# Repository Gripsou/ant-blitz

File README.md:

# ant-blitz
UV meter based on STM32

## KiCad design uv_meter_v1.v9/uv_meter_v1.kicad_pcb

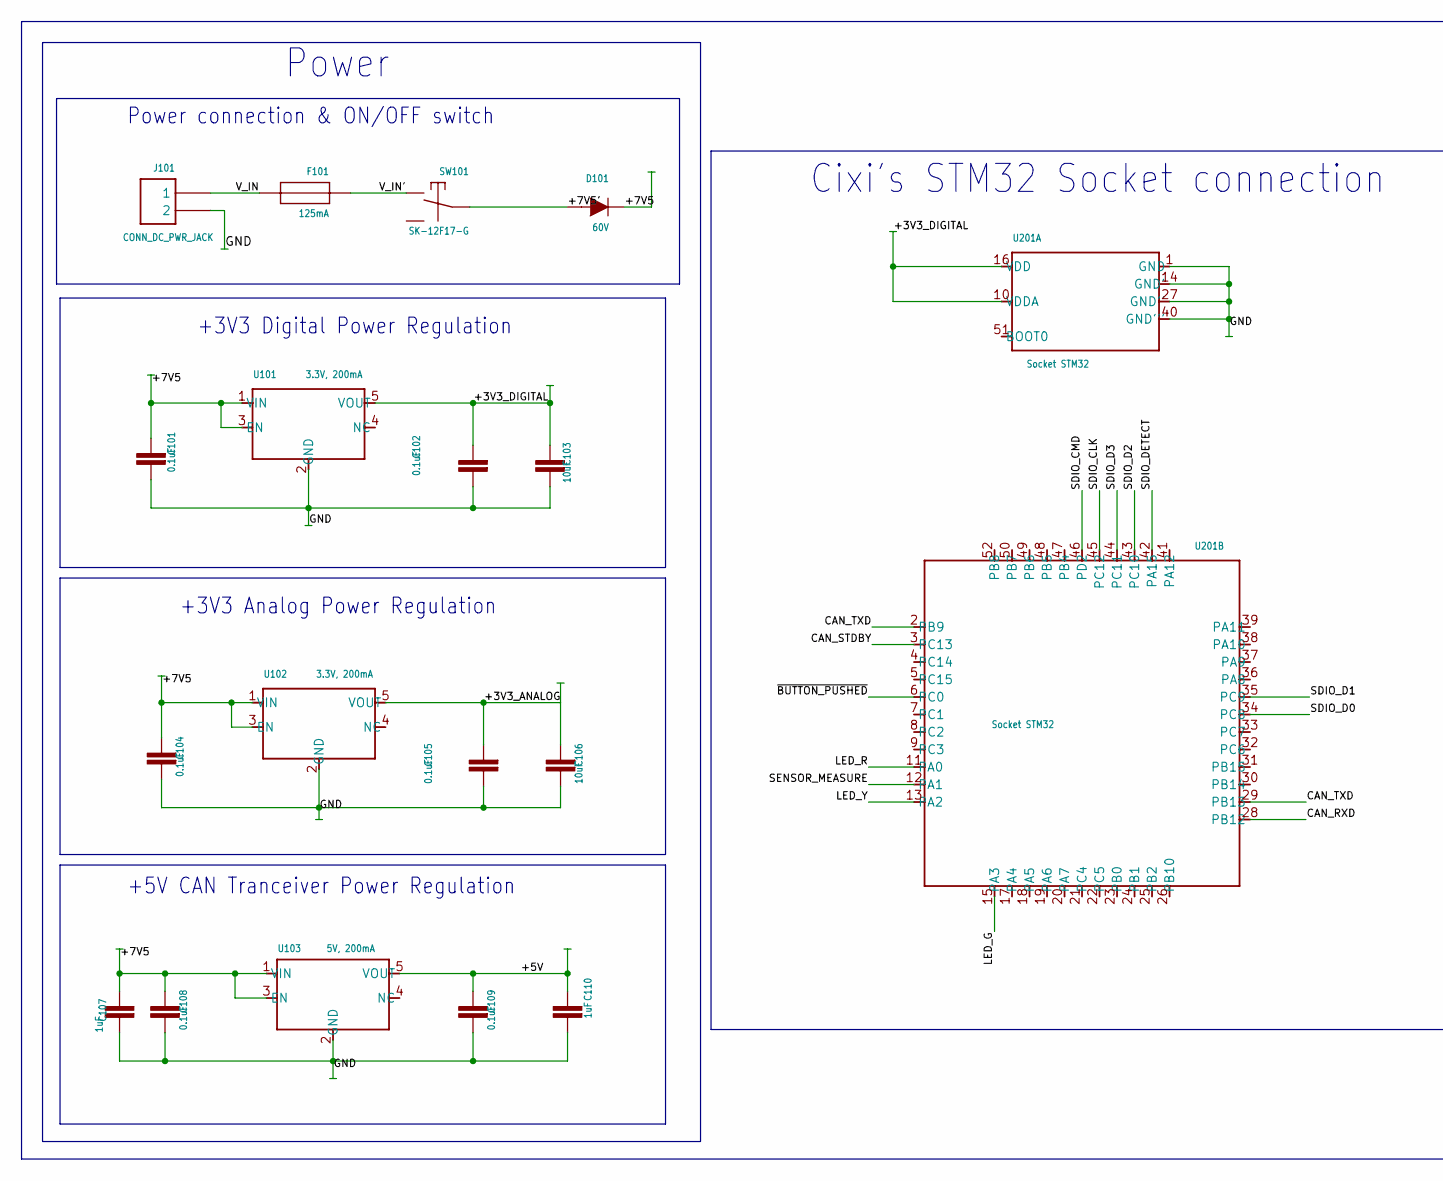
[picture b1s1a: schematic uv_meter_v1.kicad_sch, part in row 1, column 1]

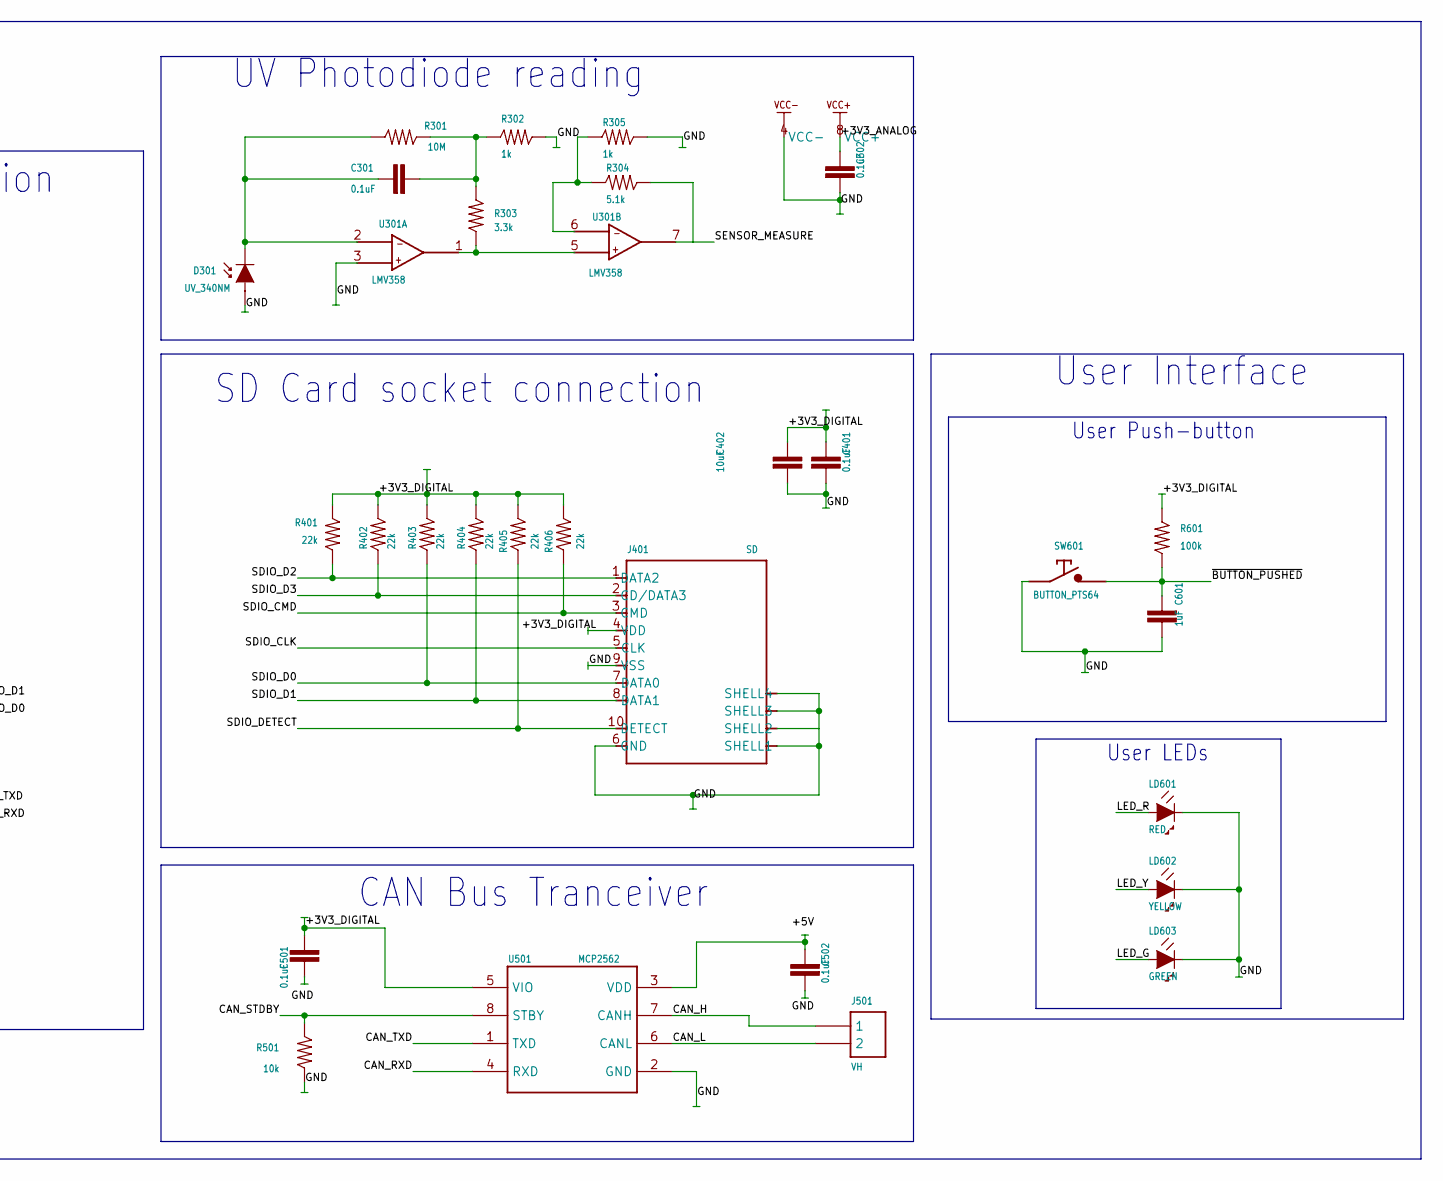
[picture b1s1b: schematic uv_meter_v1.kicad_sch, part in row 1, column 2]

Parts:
C101, C102, C104, C105, C108, C109, C301, C302, C401, C501, C502: 0.1uF; 0805_GRM
C103, C106, C402: 10uF; 0805_GRM
C107, C110, C601: 1uF; 0805_GRM
D101: 60V; SOD123_ST
D301: UV_340NM; PHOTODIODE_MOLDED
F101: 125mA; FUSE_1206
J101: CONN_DC_PWR_JACK
J401: SD; CONN_SD_5033981892
J501: VH; JST_VH_2F_SIDE
LD601: RED; LED_0805
LD602: YELLOW; LED_0805
LD603: GREEN; LED_0805
R301: 10M; RES_0805_ERJ
R302, R305: 1k; RES_0805_ERJ
R303: 3.3k; RES_0805_ERJ
R304: 5.1k; RES_0805_VISHAY
R401, R402, R403, R404, R405, R406: 22k; RES_0805_ERJ
R501: 10k; RES_0805_ERJ
R601: 100k; RES_0805_ERJ
SW101: SK-12F17-G; COMMUTATOR_SK-12F17-G
SW601: BUTTON_PTS64; BUTTON_PUSH_CK
U101, U102: 3.3V, 200mA; SOT23-5
U103: 5V, 200mA; SOT23-5
U201: Socket STM32; SOCKET_STM32
U301: LMV358; SOIC8
U501: MCP2562; SO_8

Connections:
+3V3_ANALOG: C105.1 (2), C106.1 (2), C302.2 (1), U102.5 (VOUT), U301.8 (VCC+)
+3V3_DIGITAL: C102.1 (2), C103.1 (2), C401.2 (1), C402.2 (1), C501.1 (2), J401.4 (VDD), R401.2, R402.2, R403.2, R404.2, R405.2, R406.2, R601.2, U101.5 (VOUT), U201.10 (VDDA), U201.16 (VDD), U501.5 (VIO)
+7V5: C101.1 (2), C104.1 (2), C107.1 (2), C108.1 (2), D101.K, U101.1 (VIN), U101.3 (EN), U102.1 (VIN), U102.3 (EN), U103.1 (VIN), U103.3 (EN)
+7V5': D101.A, SW101.IN
CAN_H: J501.1, U501.7 (CANH)
CAN_L: J501.2, U501.6 (CANL)
CAN_RXD: U201.28 (PB12), U501.4 (RXD)
CAN_STDBY: R501.2, U201.3 (PC13), U501.8 (STBY)
CAN_TXD: U201.2 (PB9), U201.29 (PB13), U501.1 (TXD)
GND: C101.2 (1), C102.2 (1), C103.2 (1), C104.2 (1), C105.2 (1), C106.2 (1), C107.2 (1), C108.2 (1), C109.2 (1), C110.2 (1), C302.1 (2), C401.1 (2), C402.1 (2), C501.2 (1), C502.2 (1), C601.2 (1), D301.2 (A), J101.2, J101.3 (2), J401.6 (GND), J401.9 (VSS), J401.SH1 (SHELL1), J401.SH2 (SHELL2), J401.SH3 (SHELL3), J401.SH4 (SHELL4), LD601.1 (K), LD602.1 (K), LD603.1 (K), R302.2, R305.2, R501.1, SW601.1 (C), SW601.2 (C), U101.2 (GND), U102.2 (GND), U103.2 (GND), U201.1 (GND), U201.14 (GND'), U201.27 (GND''), U201.40 (GND'''), U301.3 (IN+), U301.4 (VCC-), U501.2 (GND)
LED_G: LD603.2 (A), U201.15 (PA3)
LED_R: LD601.2 (A), U201.11 (PA0)
LED_Y: LD602.2 (A), U201.13 (PA2)
unnamed: R303.1, U301.1 (OUT), U301.5 (IN+)
unnamed: C301.1 (2), R301.2, R302.1, R303.2
unnamed: C301.2 (1), D301.1 (K), R301.1, U301.2 (IN-)
unnamed: R304.1, R305.1, U301.6 (IN-)
SDIO_CLK: J401.5 (CLK), U201.45 (PC12)
SDIO_CMD: J401.3 (CMD), R406.1, U201.46 (PD2)
SDIO_D0: J401.7 (DATA0), R403.1, U201.34 (PC8)
SDIO_D1: J401.8 (DATA1), R404.1, U201.35 (PC9)
SDIO_D2: J401.1 (DATA2), R401.1, U201.43 (PC10)
SDIO_D3: J401.2 (CD/DATA3), R402.1, U201.44 (PC11)
SDIO_DETECT: J401.10 (DETECT), R405.1, U201.42 (PA15)
SENSOR_MEASURE: R304.2, U201.12 (PA1), U301.7 (OUT)
V_IN: F101.1, J101.1
V_IN': F101.2, SW101.OUT_L (OUT_1)
~BUTTON_PUSHED: C601.1 (2), R601.1, SW601.3 (T), SW601.4 (T), U201.6 (PC0)

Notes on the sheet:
Cixi's STM32 Socket connection
User Interface
+3V3 Digital Power Regulation
+5V CAN Tranceiver Power Regulation
User Push-button
SD Card socket connection
UV Photodiode reading
CAN Bus Tranceiver
Power connection & ON/OFF switch
Power
User LEDs
+3V3 Analog Power Regulation

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
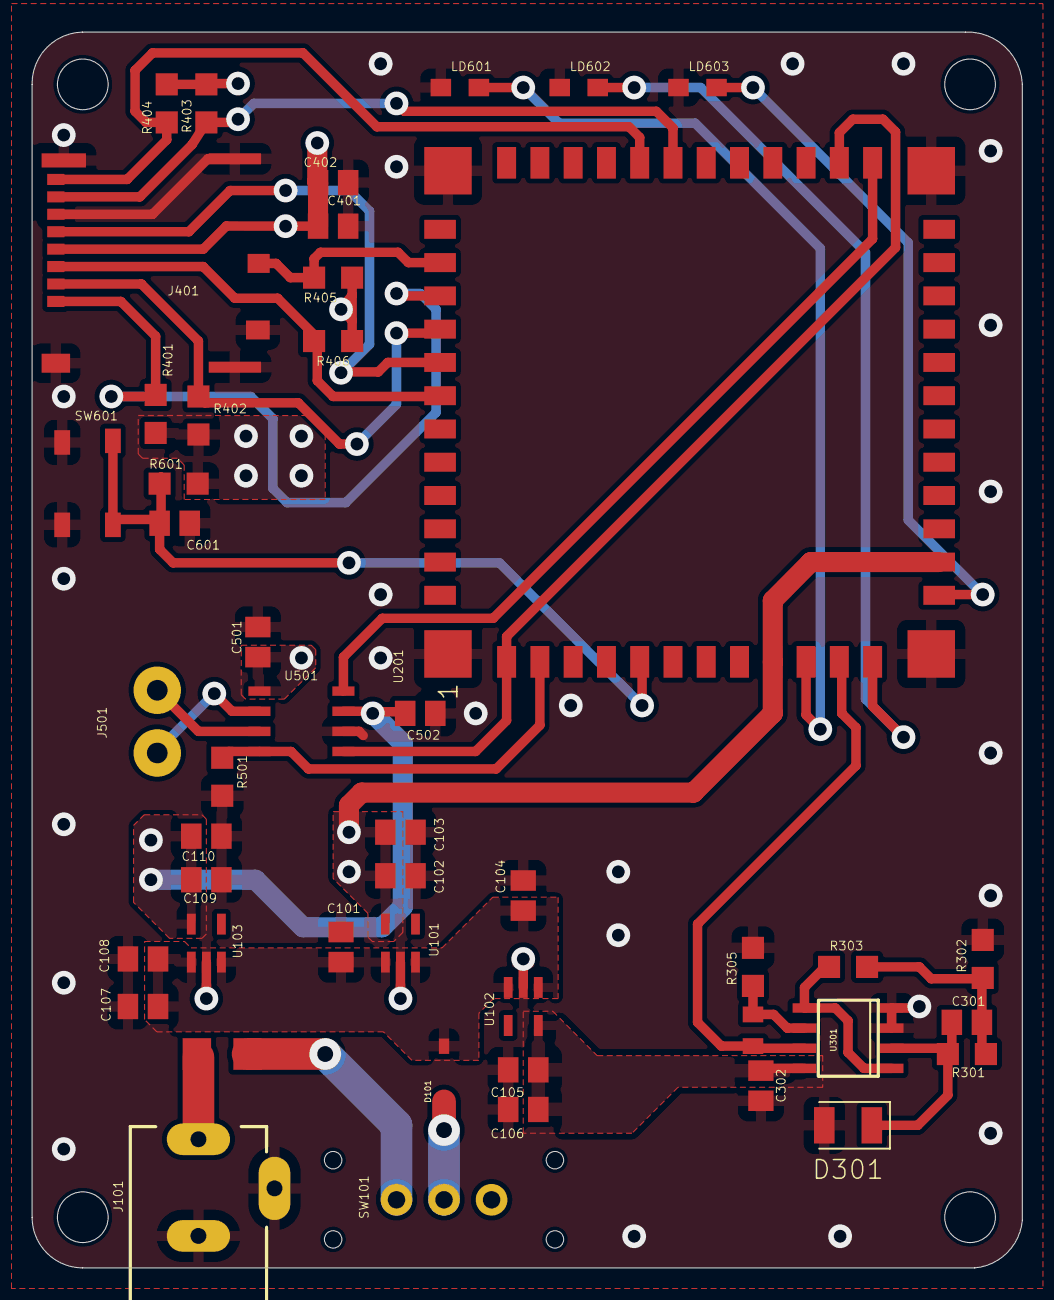
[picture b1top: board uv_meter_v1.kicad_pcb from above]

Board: 2 copper layers, 62.5 x 78.0 mm, 51 parts (0 on the bottom side), 29 nets.

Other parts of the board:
UNK_HOLE_0: dummyfp0
UNK_HOLE_1: dummyfp1
UNK_HOLE_2: dummyfp2
UNK_HOLE_3: dummyfp3

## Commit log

2025-01-14 Initial commit
    * Add "README.md"
    * Add ".gitignore" for KiCad
    * Add LICENSE
2025-01-14 Import project from EAGLE
    Import EAGLE project to KiCad 9.
2025-01-21 Move project created in KiCad 9 rc1 to dedicated forlder
    Since the project seems to have issues, it is better to isolte it in its specific folder and try it again when KiCad v9.0.0 or even v9.0.1 is released.
2025-01-21 Try new project import in KiCad 8
    Use KiCad v8.0.8 to import project and see if it fixes the 3D model issues. If yes, we might just get rid of the previous KiCad v9 rc1 import and update it to v9 once it is released
2025-01-21 Design importation fix
    * Import from Eagle has some inconsistency such as copper exclusion being attributed to "F.Courtyard" instead of "Margin".
    * Add margin where it is supposed to be.
    * Add some 3D models : local footprint library links to KiCad 8 3D models library as much as possible.
2025-01-22 Fix STM32 Socket and LDO symbols
    * Remove all `polyline` elements from symbols when not usefull.
    * Fix pin lenght, texts size and overall positions since they are not on a
    metric grid just like it is supposed to be in this particular case.
    * Add background color so the symbol looks better.
    * LDO +3V3 and +1V8 now derive from the +5V one.
2025-01-22 Update schematic from library
    Since some symbols have been updated to look better and for later and easier
    updates a schematic update from library was required.
    NOTE :
    The current goal is to fix all symbols and schematic but it should look like
    what the original project was. No symbol redesign is to be performed at this
    stage : we will tag this as the V0 since the PCB has been assembled in the
2025-01-22 Update all vias positions
    Import from original project has placed geometric shapes on an imperial grid.
    Therefore, we need to place them back on a metric grid.
    => this has been done for all vias in the current commit.
2025-02-24 Update LMV358 symbol
    * Update LMV358 symbol in local library : use shapes that allow to fill
    symbol and break power supply sub-symbol into 2 different entities
    for ease of use reasons.
    * Update design schematic accordingly.
2025-02-24 Add one picture of actual PCB
    Add a picture of the system as it was assembled. The picture shows the
    photodiode reading SMD assembly.
2025-03-01 Update to KiCad V9.0.0
    Update project files to KiCad V9.0.0. Apparently a few changes were brought to the software and configuration files since the release candidate 1
2025-04-15 Update Power symbols in schematic
    * Remove old power "symbols" created with labels and make use of KiCad's
    power symbols from standard library instead
    * Place unconnected marks where required. This will comply with KiCad's
    standards if any ERC check is performed
2025-04-20 Update MCP2562 symbol
    Update MCP2562 CAN transceiver symbol so it corresponds to my KiCad standards and look better in schematic
2025-05-21 Update Capacitors symbols in library
    * Create generic capacitor symbol out of 100 nF one.
    * Update symbol's graphical elements so they are handled in an easier
    way in KiCad.
    * Make all capcitor values derivatives from the generic "C" symbol
    i.e. 100 nF, 1 µF and 10 µF.
2025-05-21 Update Resistor symbols in library
    * Create generic resistor symbol
    * Update symbol's graphical elements so they are handled in an easier
    way in KiCad.
    * Make all resistor values derivatives from the generic "R" symbol
2025-05-21 Update Socket position in schematic
    Symbol was updated to fit the grid but its position in schematic had to
    be updated. Now done
2025-05-28 Update power jack symbol
    Update power jack symbol so it is less quirky and is designed according
    to the 0,25mm grid.
2025-05-28 Update SD card connector symbol
    * Update all geometrical shapes in symbol in order to remove uneccessary
    lines : make use of pin and rectangles when appropriate.
    * Update all pins lengths and text
    * Center component on (0,0) coordinates.
    * Add background color
2025-05-28 Update power jack and SD card connector in schematic
    * Update components according to their library counterparts :
    - SD Card connector
    - DC power jack
    * Update schematic to fix disrepencies due to components updates
2025-06-04 Update diodes symbols
    * Create generic symbol for LEDs :
    - Originally a duplicate from ```LED_GREEN_0805```
    - Make symbol fit 0,2500 mm grid.
    - Update graphical elements so there aren't too many.
    * Make all LEDs derivatives of the new generic symbol
    * Update photodiode symbol accordingly
2025-06-04 Update some capacitors and resistors
    * Update schematic with 100nF capacitors from library.
    * Update schematic with 1k resistor from library.
    * All updated components now fit schematic grid.
